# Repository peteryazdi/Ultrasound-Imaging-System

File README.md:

# Multi-Channel Ultrasound Imaging System

An ultrasound imaging system built from scratch: high-voltage transmit electronics, a receive chain, digitization and FPGA beamforming. Self-funded personal project.

<p align="center">
  
  <br>
  <sub>Rev 0 two-channel transmit pulser, powered on the bench.</sub>
</p>

## Status

| Stage | Scope | Status |
|---|---|---|
| Single-channel prototype | MSP430 board, custom PCB, 5 MHz piezo, envelope detection | Done |
| [Rev 0](rev0/README.md) | 2-channel high-voltage transmit pulser | Built, brought up, tested in water |
| [Rev 1](rev1/README.md) | 4-channel, 5 MHz transmit and receive: power module and Tx/Rx board | In design |
| Later | ADC capture on the FPGA, delay-and-sum beamforming, B-mode images of a phantom | Planned |

Each revision has its own page with the design, files and results.

## Where it started

The project started as a single-channel system: an MSP430 board, a custom PCB and a 5 MHz piezo probe. Envelope detection kept the signal within the ADC's limits and was enough to tell skin from bone.

## Physics reference

| Quantity | Formula | Value at 5 MHz |
|---|---|---|
| Wavelength | λ = c / f | 0.308 mm |
| Axial resolution | c / (2f) per cycle | 0.154 mm |
| Depth from echo time | d = ct / 2 | 0.77 mm/µs |
| Max PRF | c / (2 × d_max) | 7700 Hz at 10 cm |
| Attenuation | ~0.5 dB/cm/MHz | 2.5 dB/cm |
| Sound speed (soft tissue) | | 1540 m/s |

## Repository layout

```
docs/images/   Photos, scope captures and block diagrams
rev0/          Rev 0 transmit pulser: KiCad project, fabrication files, test results
rev1/          Rev 1 power module and Tx/Rx board (in design)
```

## Getting the files

```bash
cd ~/Desktop
git clone https://github.com/peteryazdi/Ultrasound-Imaging-System.git
```

This works in Terminal on macOS and Linux and in PowerShell on Windows. Open the `.kicad_pro` files with KiCad 10.

## Safety

This is an educational project, not a certified medical device, and it is not intended for diagnostic or clinical use. The high-voltage circuits need appropriate safety practices. Acoustic output has not been characterized, so testing is done into water baths and phantoms.

## License

MIT. See [LICENSE](LICENSE).

## Author

Peter Yazdi, [peteryazdi@gmail.com](mailto:peteryazdi@gmail.com)

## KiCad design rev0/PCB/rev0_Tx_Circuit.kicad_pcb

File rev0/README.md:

# Rev 0: two-channel transmit pulser

Rev 0 is a 4-layer board that drives two transducers with bipolar high-voltage pulses. It was the first step: get the transmit side working and see echoes in water before building a receive chain.

**Status:** done. Built, brought up and tested in water.

## Board

On each channel an MD1213 gate driver switches a TC6320 complementary MOSFET pair between the +HV and -HV rails. The gate drive is AC-coupled through 10 nF / 200 V capacitors, so the ±5 V driver outputs can control MOSFETs whose sources sit on the high-voltage rails. Back-to-back ES1D diodes clamp each transmit node, and each channel leaves the board on an SMA connector.

An LM2776 charge pump makes the negative driver rail from the single +5 V input. The HV rails have bulk and ceramic decoupling and 1 MΩ bleed resistors so they discharge when the supplies are off. The pulse inputs (INA, INB), output enable and trigger lines come in on a 2×5 header with 10 kΩ pull-downs, so the outputs stay off at power-up. HV nets are routed in their own net class with 0.5 mm clearance and 0.5 mm tracks.

The switching stage was simulated in LTspice before layout. The board was designed in KiCad and ordered from JLCPCB.

## Specs

| Parameter | Value |
|---|---|
| Channels | 2 |
| Board | 4 layers, KiCad |
| HV rails | Designed for ±100 V, tested to ±60 V (limit of the bench supplies) |
| MOSFET pair | TC6320, 200 V |
| Gate drive | ±5 V, AC-coupled |
| Test pattern | 5 MHz, 60 ns per half-cycle with 40 ns dead time, 1 to 7 cycles, 1 kHz PRF |
| Measured frequency | 5.000 MHz (200 ns period) |

## Files

| Folder or file | Contents |
|---|---|
| [`PCB/`](PCB/) | KiCad project |
| [`PCB/rev0_Tx_Circuit.pdf`](PCB/rev0_Tx_Circuit.pdf) | Schematic |
| [`PCB/jlcpcb/production_files/`](PCB/jlcpcb/production_files/) | Gerbers, BOM and placement files sent for fabrication |
| [`testing/`](testing/) | Bring-up procedure, test report, LTspice model, DRC and ERC reports |
| [`datasheets/`](datasheets/) | Datasheets for the key parts |

## Results

The board was brought up in four stages, each with an acceptance criterion that had to pass before moving on. The full write-ups are in the [bring-up procedure](testing/Rev0_TX_Pulser_Bring-Up_Procedure.pdf) and the [test report](testing/Rev0_TX_Pulser_Test_Report.pdf).

<p align="center">

  <br>
  <sub>Left: bench supplies, breadboard rail distribution, AD2 pattern generator and the board. Right: the full setup with the water tank.</sub>
</p>

1. **Unpowered checks.** Every reachable net checked for continuity and resistance against the layout. No solder faults, no rail-to-ground shorts.
2. **Power only.** HV rails walked up from 10 V with a 0.5 A current limit. The charge pump produced both driver rails, and with output enable held low both outputs stayed at 0 V at full rail voltage. Every later step depends on that interlock.
3. **First enable.** INA, INB and output enable from an AD2, verified on its logic analyzer before connecting. Clean bipolar switching into a 220 pF dummy load, with amplitude tracking the rail voltage.
4. **Water tank.** A second 5 MHz element used as an independent receiver. The received burst measures 200 ns per period (5.000 MHz). A target about 1 cm away returned an echo at 14 to 15 µs, consistent with the round trip at the speed of sound in water. Ring-down was 4 to 5 cycles with the transducer in air and close to none with its face in water.

<p align="center">

  <br>
  <sub>Left: received burst, cursors one period apart (200 ns, 5.000 MHz). Right: transmit feedthrough at t = 0 and the water-path echo 29 µs later.</sub>
</p>

**What didn't work, and why.** I could not resolve an interface below the front surface of a tissue target. The numbers rule out weak reflection and attenuation over a few millimetres. The real limits are on the receive side. The echoes are raw transducer output going straight into the scope, with no amplifier, filter or time-gain compensation, so millivolt returns sit near the noise floor. Transmit feedthrough and ring-down also blank the first few microseconds, which is exactly where a shallow interface returns. Raising the transmit voltage would scale the feedthrough along with the echo, so the next board is the receive chain rather than more drive.

**Open items**

- Switching times are not measured yet. The 100 MHz scope can't resolve edges faster than about 3.5 ns.
- Transducer capacitance is estimated at 220 pF and needs an impedance measurement.
- Dead time can't be safely reduced until a current-sense resistor on the HV rail can show shoot-through on the scope.
- The tests need a tissue-mimicking phantom with targets at known depths in place of hand-held targets.

## Test setup

- Tektronix TDS 2014 oscilloscope (100 MHz, 1 GS/s)
- Digilent Analog Discovery 2 as the pattern generator and logic analyzer
- Bench supplies, two 0 to 30 V units in series per HV rail plus a fixed 5 V unit
- 5 MHz thickness-gauge transducers with Lemo connectors, through SMA-to-Lemo adapters

## Getting the files

```bash
cd ~/Desktop
git clone https://github.com/peteryazdi/Ultrasound-Imaging-System.git
```

This works in Terminal on macOS and Linux and in PowerShell on Windows. Open `rev0/PCB/rev0_Tx_Circuit.kicad_pro` with KiCad 10.

## License

MIT. See [LICENSE](../LICENSE).

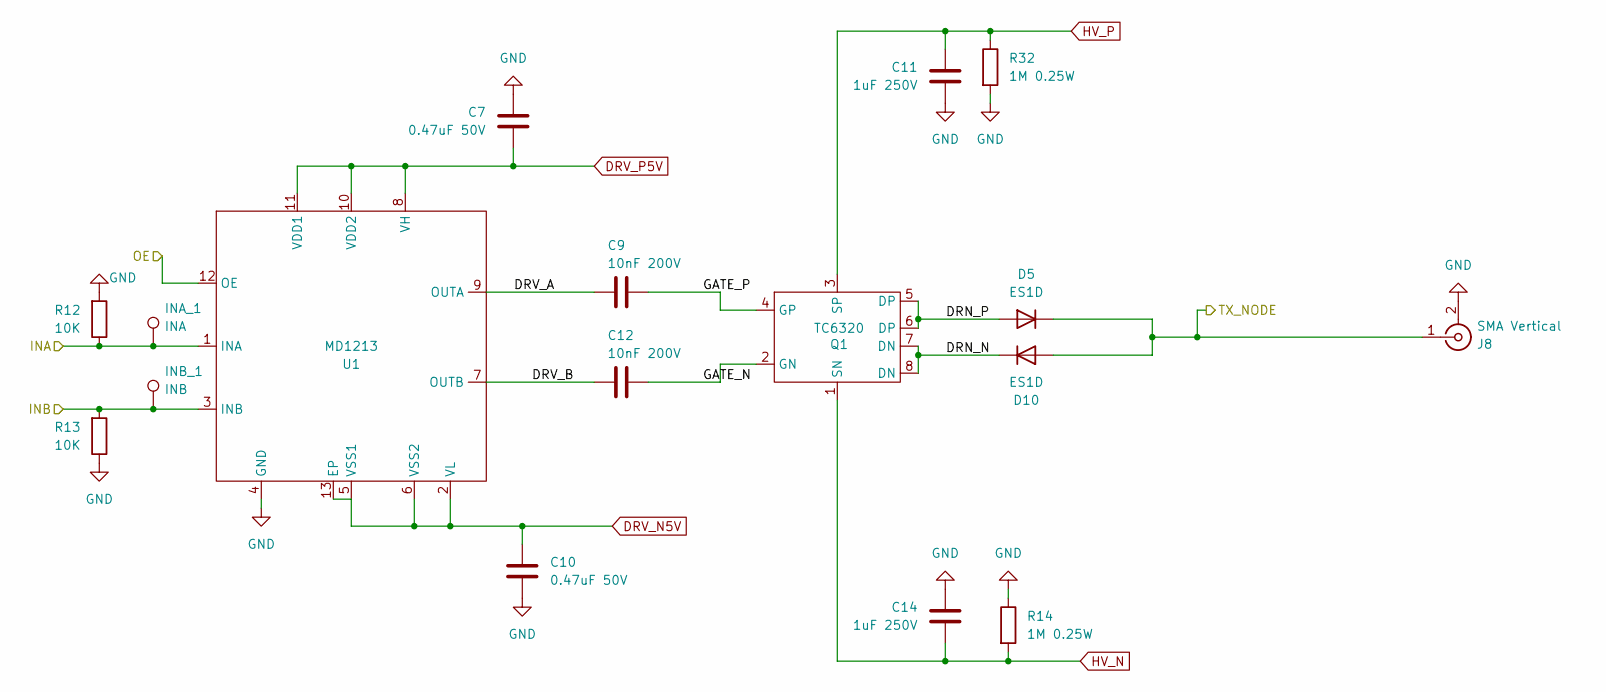
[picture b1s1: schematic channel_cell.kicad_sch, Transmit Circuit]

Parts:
C7, C10: 0.47uF 50V; C_0805_2012Metric; Voltage Rating 50V
C9, C12: 10nF 200V; C_0805_2012Metric; Voltage Rating 200V
C11, C14: 1uF 250V; C_1812_4532Metric; Voltage Rating 250V
D5, D10: ES1D; D_SMA; Voltage Rating 200V; Power Rating 1A, 15ns recovery, 30A IFSM
INA_1: INA; TestPoint_THTPad_D1.5mm_Drill0.7mm
INB_1: INB; TestPoint_THTPad_D1.5mm_Drill0.7mm
J8: SMA Vertical; SMA_Amphenol_132289_EdgeMount
Q1: TC6320; SOIC-8_3.9x4.9mm_P1.27mm; Voltage Rating BVDSS: 200V; Power Rating 2A continuous
R12, R13: 10K; R_0805_2012Metric; Voltage Rating 150V; Power Rating 0.125W
R14, R32: 1M 0.25W; R_Axial_DIN0207_L6.3mm_D2.5mm_P10.16mm_Horizontal; Voltage Rating 250V; Power Rating 0.25 W
U1: MD1213; MD1213_VQFN12_4x4_P0.8_EP1.7x1.7; Voltage Rating VDD-VSS: 13V max; Power Rating 2A peak output

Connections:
/CONTROL_IO/CH1_INA: INA_1.1 (1_1), R12.1, U1.1 (INA); also elsewhere on the board
/CONTROL_IO/CH1_INB: INB_1.1 (1_1), R13.2, U1.3 (INB); also elsewhere on the board
/CONTROL_IO/CH1_OE: U1.12 (OE); also elsewhere on the board
/CONTROL_IO/TX_Node_1: D5.1 (K), D10.2 (A), J8.1 (In); also elsewhere on the board
/TX_1/DRN_N: D10.1 (K), Q1.7 (DN), Q1.8 (DN)
/TX_1/DRN_P: D5.2 (A), Q1.5 (DP), Q1.6 (DP)
/TX_1/DRV_A: C9.1, U1.9 (OUTA)
/TX_1/DRV_B: C12.1, U1.7 (OUTB)
/TX_1/GATE_N: C12.2, Q1.2 (GN)
/TX_1/GATE_P: C9.2, Q1.4 (GP)
DRV_N5V: C10.2, U1.2 (VL), U1.5 (VSS1), U1.6 (VSS2), U1.13 (EP); also elsewhere on the board
DRV_P5V: C7.1, U1.8 (VH), U1.10 (VDD2), U1.11 (VDD1); also elsewhere on the board
GND: C7.2, C10.1, C11.2, C14.1, J8.2 (Ext), R12.2, R13.1, R14.1, R32.2, U1.4 (GND); also elsewhere on the board
HV_N: C14.2, Q1.1 (SN), R14.2; also elsewhere on the board
HV_P: C11.1, Q1.3 (SP), R32.1; also elsewhere on the board

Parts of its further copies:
C13, C16: 0.47uF 50V; C_0805_2012Metric; Voltage Rating 50V
C15, C18: 10nF 200V; C_0805_2012Metric; Voltage Rating 200V
C17, C21: 1uF 250V; C_1812_4532Metric; Voltage Rating 250V
D9, D11: ES1D; D_SMA; Voltage Rating 200V; Power Rating 1A, 15ns recovery, 30A IFSM
INA_2: INA; TestPoint_THTPad_D1.5mm_Drill0.7mm
INB_2: INB; TestPoint_THTPad_D1.5mm_Drill0.7mm
J9: SMA Vertical; SMA_Amphenol_132289_EdgeMount
Q2: TC6320; SOIC-8_3.9x4.9mm_P1.27mm; Voltage Rating BVDSS: 200V; Power Rating 2A continuous
R15, R16: 10K; R_0805_2012Metric; Voltage Rating 150V; Power Rating 0.125W
R17, R37: 1M 0.25W; R_Axial_DIN0207_L6.3mm_D2.5mm_P10.16mm_Horizontal; Voltage Rating 250V; Power Rating 0.25 W
U2: MD1213; MD1213_VQFN12_4x4_P0.8_EP1.7x1.7; Voltage Rating VDD-VSS: 13V max; Power Rating 2A peak output

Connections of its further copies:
/CONTROL_IO/CH2_INA: INA_2.1 (1_1), R15.1, U2.1 (INA); also elsewhere on the board
/CONTROL_IO/CH2_INB: INB_2.1 (1_1), R16.2, U2.3 (INB); also elsewhere on the board
/CONTROL_IO/CH2_OE: U2.12 (OE); also elsewhere on the board
/CONTROL_IO/TX_Node_2: D9.1 (K), D11.2 (A), J9.1 (In); also elsewhere on the board
/TX_2/DRN_N: D11.1 (K), Q2.7 (DN), Q2.8 (DN)
/TX_2/DRN_P: D9.2 (A), Q2.5 (DP), Q2.6 (DP)
/TX_2/DRV_A: C15.1, U2.9 (OUTA)
/TX_2/DRV_B: C18.1, U2.7 (OUTB)
/TX_2/GATE_N: C18.2, Q2.2 (GN)
/TX_2/GATE_P: C15.2, Q2.4 (GP)
DRV_N5V: C16.2, U2.2 (VL), U2.5 (VSS1), U2.6 (VSS2), U2.13 (EP); also elsewhere on the board
DRV_P5V: C13.1, U2.8 (VH), U2.10 (VDD2), U2.11 (VDD1); also elsewhere on the board
GND: C13.2, C16.1, C17.2, C21.1, J9.2 (Ext), R15.2, R16.1, R17.1, R37.2, U2.4 (GND); also elsewhere on the board
HV_N: C21.2, Q2.1 (SN), R17.2; also elsewhere on the board
HV_P: C17.1, Q2.3 (SP), R37.1; also elsewhere on the board

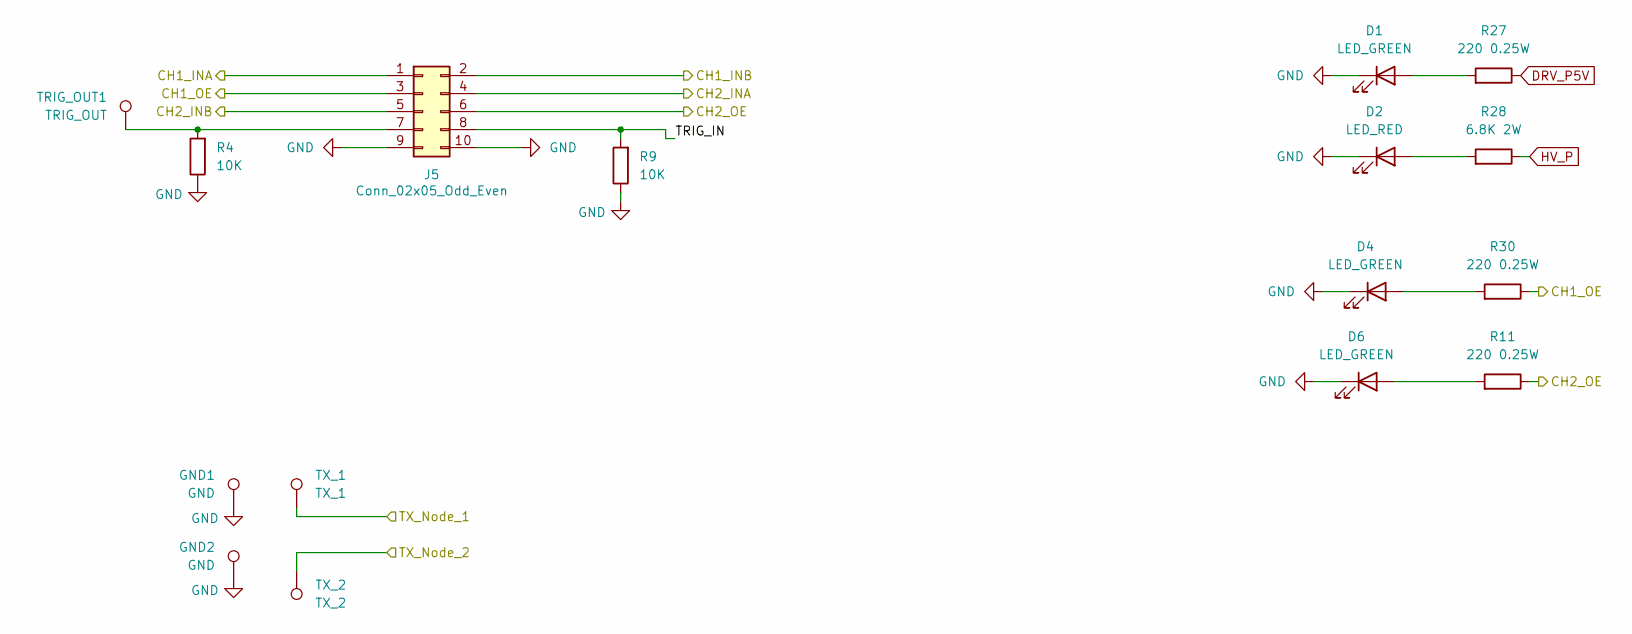
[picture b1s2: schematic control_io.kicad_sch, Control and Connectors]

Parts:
D1, D4, D6: LED_GREEN; LED_D3.0mm
D2: LED_RED; LED_D3.0mm
GND1, GND2: GND; TestPoint_THTPad_D1.5mm_Drill0.7mm
J5: Conn_02x05_Odd_Even; PinHeader_2x05_P2.54mm_Vertical; Voltage/Current 3.3V logic
R4, R9: 10K; R_Axial_DIN0207_L6.3mm_D2.5mm_P10.16mm_Horizontal; Voltage Rating 250V; Power Rating 0.25W
R11, R27, R30: 220 0.25W; R_Axial_DIN0207_L6.3mm_D2.5mm_P10.16mm_Horizontal
R28: 6.8K 2W; R_Axial_DIN0617_L17.0mm_D6.0mm_P20.32mm_Horizontal
TRIG_OUT1: TRIG_OUT; TestPoint_THTPad_D1.5mm_Drill0.7mm
TX_1: TX_1; TestPoint_THTPad_D1.5mm_Drill0.7mm
TX_2: TX_2; TestPoint_THTPad_D1.5mm_Drill0.7mm

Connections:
/CONTROL_IO/CH1_INA: J5.1; also elsewhere on the board
/CONTROL_IO/CH1_INB: J5.2; also elsewhere on the board
/CONTROL_IO/CH1_OE: J5.3, R30.1; also elsewhere on the board
/CONTROL_IO/CH2_INA: J5.4; also elsewhere on the board
/CONTROL_IO/CH2_INB: J5.5; also elsewhere on the board
/CONTROL_IO/CH2_OE: J5.6, R11.1; also elsewhere on the board
/CONTROL_IO/TRIG_IN: J5.8, R9.2
/CONTROL_IO/TX_Node_1: TX_1.1 (1_1); also elsewhere on the board
/CONTROL_IO/TX_Node_2: TX_2.1 (1_1); also elsewhere on the board
DRV_P5V: R27.1; also elsewhere on the board
GND: D1.1 (K), D2.1 (K), D4.1 (K), D6.1 (K), GND1.1 (1_1), GND2.1 (1_1), J5.9, J5.10, R4.1, R9.1; also elsewhere on the board
HV_P: R28.1; also elsewhere on the board
unnamed: D1.2 (A), R27.2
unnamed: D2.2 (A), R28.2
unnamed: D4.2 (A), R30.2
unnamed: D6.2 (A), R11.2
unnamed: J5.7, R4.2, TRIG_OUT1.1 (1_1)

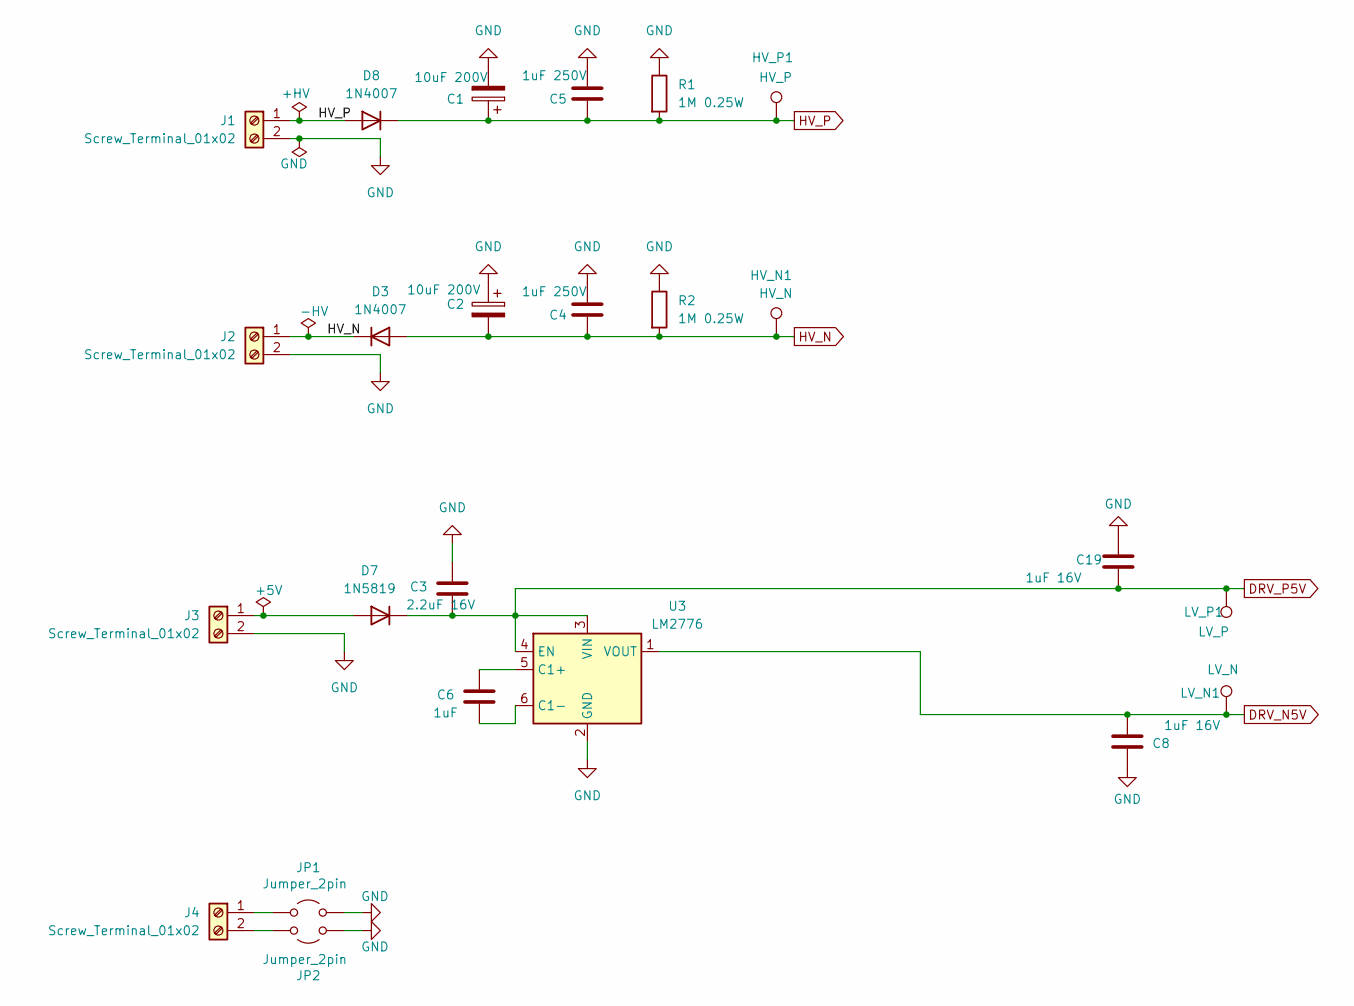
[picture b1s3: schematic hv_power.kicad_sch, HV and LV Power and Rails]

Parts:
C1, C2: 10uF 200V; CP_Radial_D8.0mm_P3.50mm; Voltage Rating 200V
C3: 2.2uF 16V; C_0805_2012Metric; Votlage Rating 16V
C4, C5: 1uF 250V; C_1812_4532Metric; Voltage Rating 250V
C6: 1uF; C_0805_2012Metric
C8, C19: 1uF 16V; C_0805_2012Metric; Votlage Rating 16V
D3, D8: 1N4007; D_DO-41_SOD81_P10.16mm_Horizontal; Voltage Rating 1000V reverse; Current Rating 1A forward
D7: 1N5819; D_DO-41_SOD81_P10.16mm_Horizontal; Voltage Rating 40V reverse; Current Rating 1A forward
HV_N1: HV_N; TestPoint_THTPad_D1.5mm_Drill0.7mm
HV_P1: HV_P; TestPoint_THTPad_D1.5mm_Drill0.7mm
J1, J2: Screw_Terminal_01x02; TerminalBlock_Phoenix_MKDS-3-2-5.08_1x02_P5.08mm_Horizontal; Voltage/Current 200V / 3A
J3: Screw_Terminal_01x02; TerminalBlock_Phoenix_MKDS-3-2-5.08_1x02_P5.08mm_Horizontal; Voltage/Current 16V / 1A
J4: Screw_Terminal_01x02; TerminalBlock_Phoenix_MKDS-3-2-5.08_1x02_P5.08mm_Horizontal
JP1, JP2: Jumper_2pin; PinHeader_1x02_P2.54mm_Vertical
LV_N1: LV_N; TestPoint_THTPad_D1.5mm_Drill0.7mm
LV_P1: LV_P; TestPoint_THTPad_D1.5mm_Drill0.7mm
R1: 1M 0.25W; Voltage Rating 250V; Power Rating 0.25 W
R2: 1M 0.25W; R_Axial_DIN0207_L6.3mm_D2.5mm_P10.16mm_Horizontal; Voltage Rating 250V; Power Rating 0.25 W
U3: LM2776; SOT-23-6

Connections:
DRV_N5V: C8.1, LV_N1.1 (1_1), U3.1 (VOUT); also elsewhere on the board
DRV_P5V: C3.1, C19.1, D7.1 (K), LV_P1.1 (1_1), U3.3 (VIN), U3.4 (EN); also elsewhere on the board
GND: C1.2, C2.1, C3.2, C4.1, C5.1, C8.2, C19.2, J1.2, J2.2, J3.2, JP1.2 (B), JP2.2 (B), R1.1, R2.1, U3.2 (GND); also elsewhere on the board
HV_N: C2.2, C4.2, D3.1 (K), D3.2 (A), HV_N1.1 (1_1), J2.1, R2.2; also elsewhere on the board
HV_P: C1.1, C5.2, D8.1 (K), D8.2 (A), HV_P1.1 (1_1), J1.1, R1.2; also elsewhere on the board
unnamed: D7.2 (A), J3.1
unnamed: J4.1, JP1.1 (A)
unnamed: J4.2, JP2.1 (A)
unnamed: C6.2, U3.5 (C1+)
unnamed: C6.1, U3.6 (C1-)

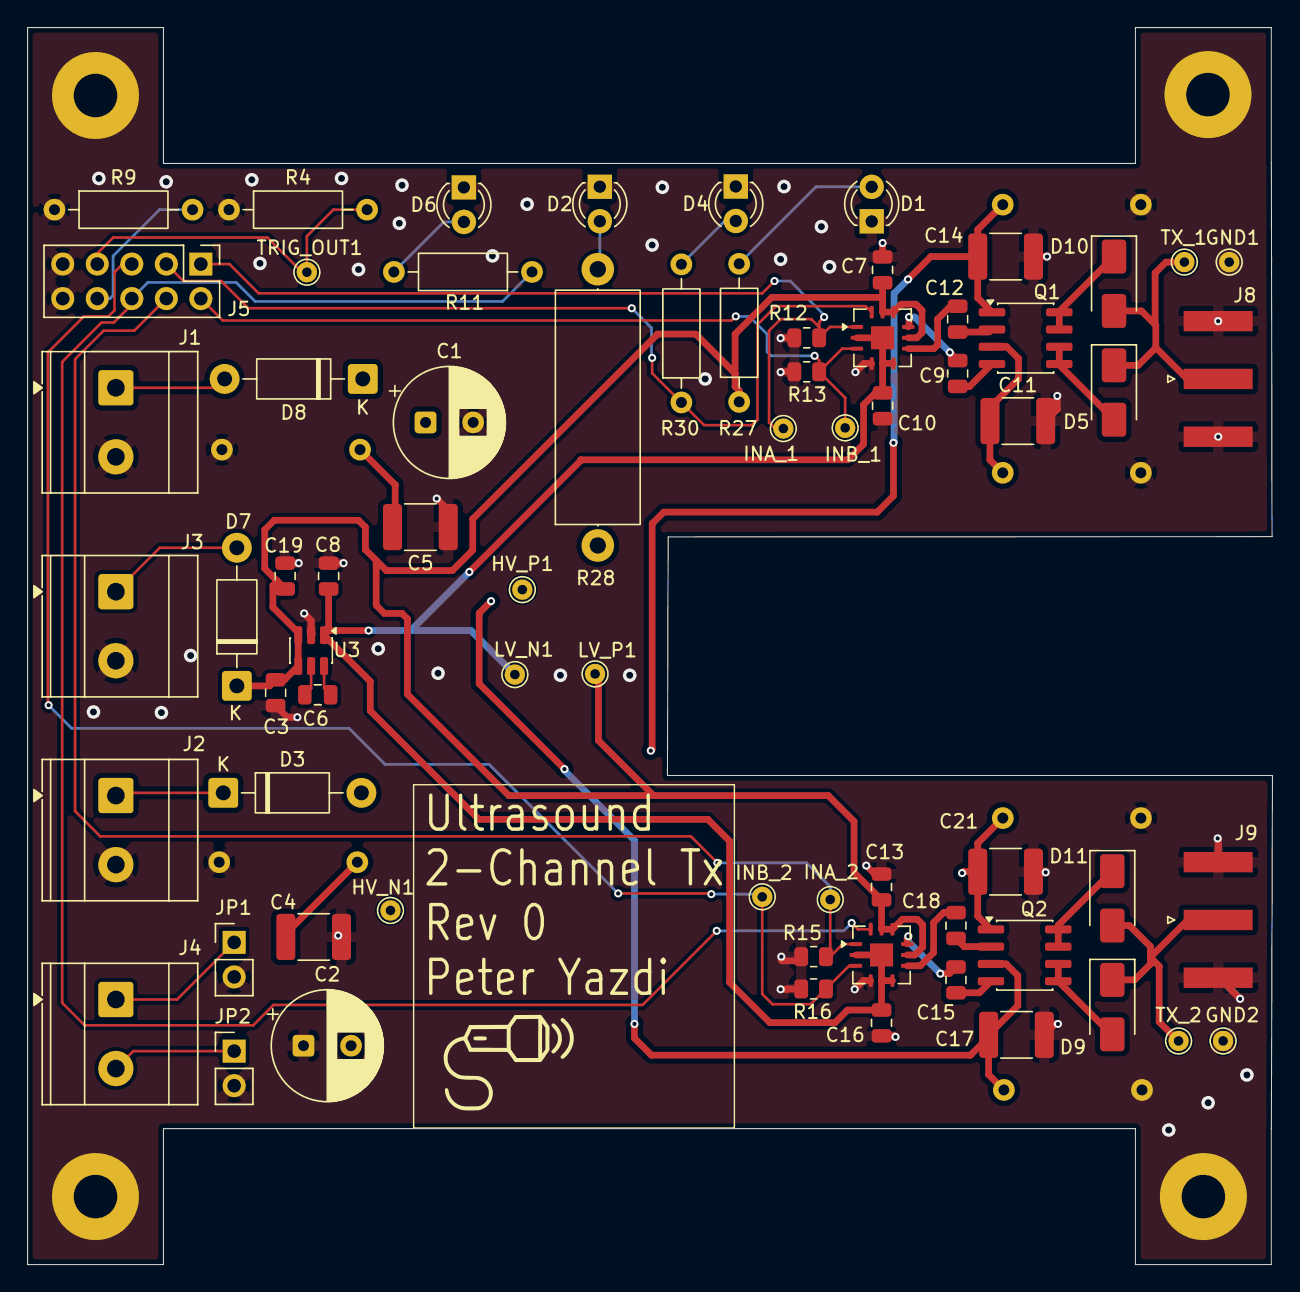
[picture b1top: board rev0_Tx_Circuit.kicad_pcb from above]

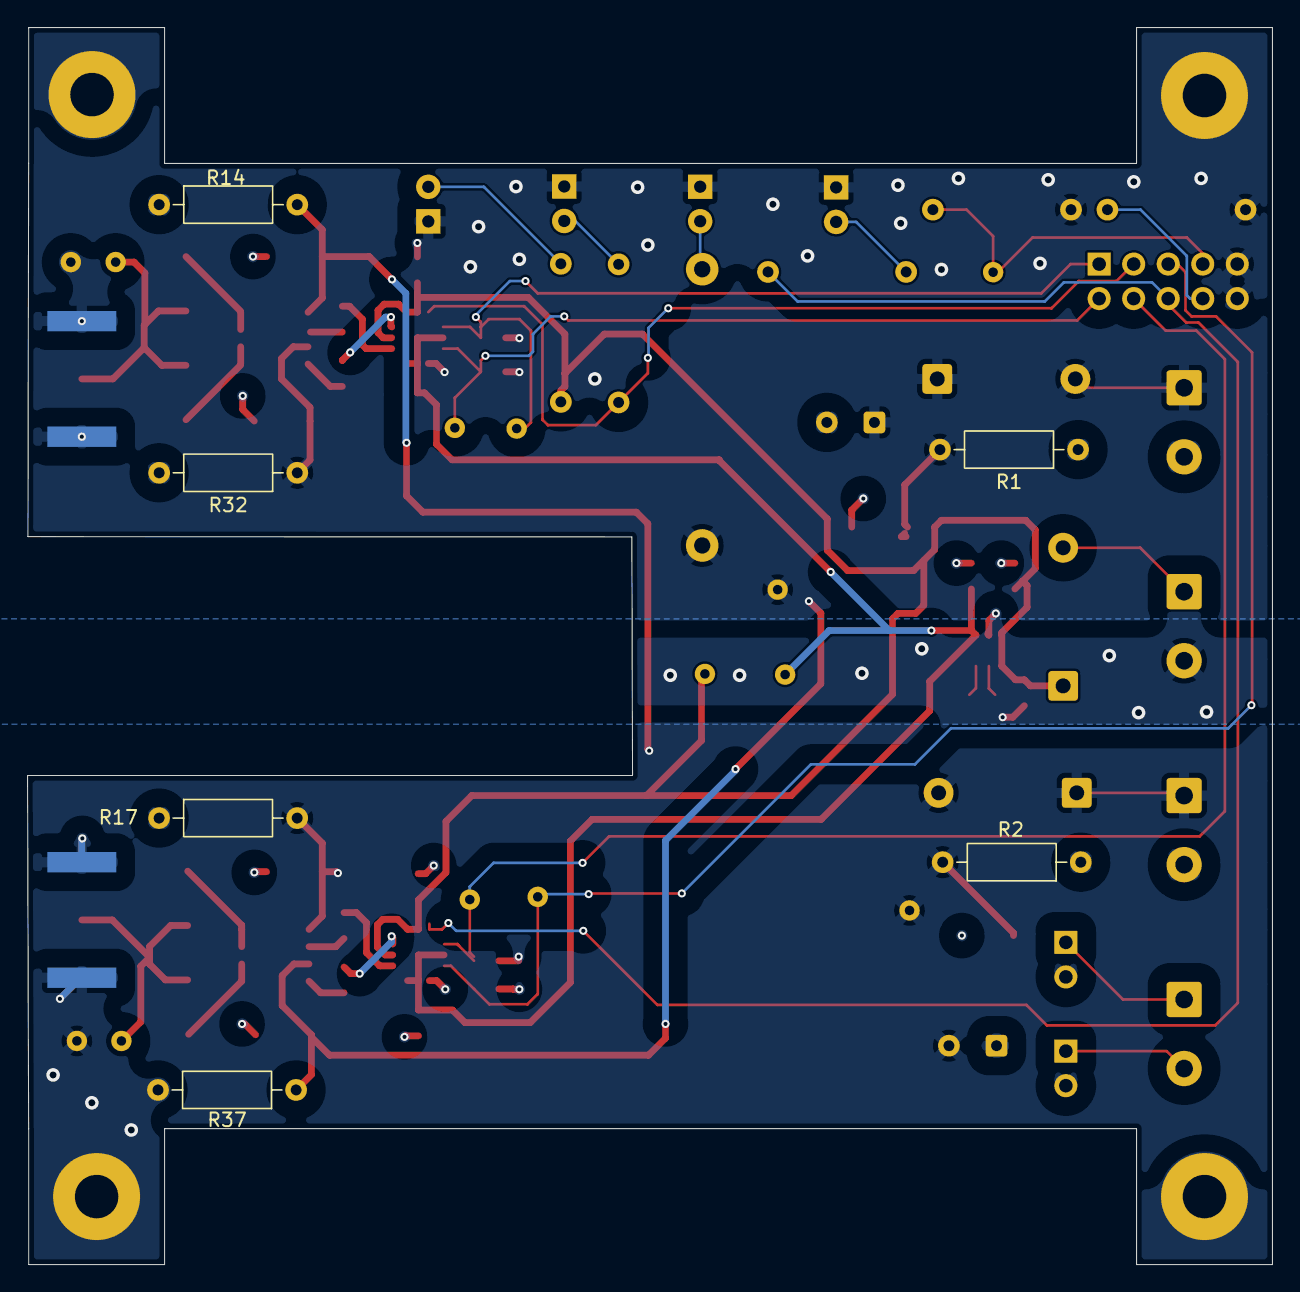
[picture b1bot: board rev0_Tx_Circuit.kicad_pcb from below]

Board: 4 copper layers, 91.6 x 91.0 mm, 74 parts (6 on the bottom side), 36 nets.
